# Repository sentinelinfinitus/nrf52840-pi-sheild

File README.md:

nrf52840 pi sheild

please note that this project is open for all to use and edit there own copy

time for a little background spec's for this project

the nrf52840 chip is to act as in a ncp format (more info on this below)
please note that this is the soc used in the project https://www.mouser.ca/ProductDetail/949-NRF52840-QIAA-R

more info of the soc here https://www.nordicsemi.com/Products/Low-power-short-range-wireless/nRF52840
data sheet https://www.mouser.ca/datasheet/2/297/nRF52840_OPS_v0.5-1074816.pdf
as of writing this these are to be broken out from the soc for later use

[please note]
Communication between the NCP and the host processor is via serial interface, typically using SPI or UART, over the Spinel protocol.
https://openthread.io/guides/ncp

UART, SPI, TWI, PDM, I2S, QSPI
PWM , other io
NFC-A
USB 2.0

{
[this is pulled from https://openthread.io/platforms/#network-co-processor-ncp   ]
Network Co-Processor (NCP)

The standard NCP design has Thread features on the SoC and runs the application layer on a host processor,
which is typically more capable (but has greater power demands) than the OpenThread device.
The host processor communicates with the OpenThread device via a serial interface (typically SPI or UART) over the Spinel protocol.

The benefit of this design is that the higher-power host can sleep while the 
lower-power OpenThread device remains active to maintain its place in the Thread network.
And since the SoC is not tied to the application layer,
development and testing of applications is independent of the OpenThread build.

This design is useful for gateway devices or devices that have other processing demands like IP cameras and speakers.

For more information, see NCP Support.
}

other helpfull links
https://openthread.io/guides/ncp/
https://openthread.io/guides/ncp/firmware#nordic_semiconductor_nrf52840
https://openthread.io/platforms/nrf52840

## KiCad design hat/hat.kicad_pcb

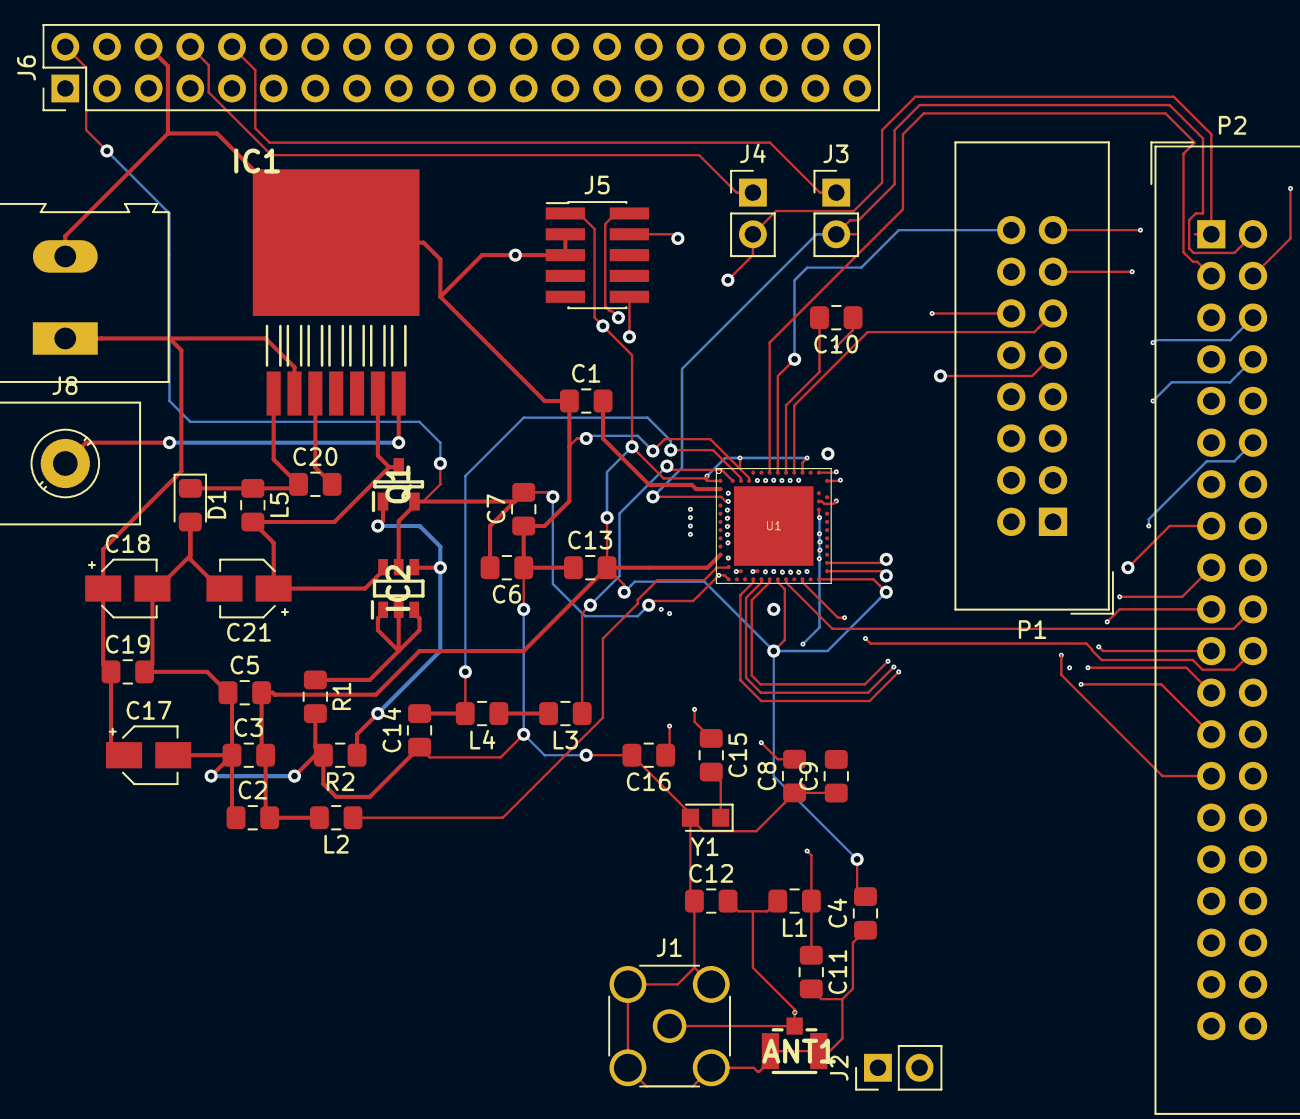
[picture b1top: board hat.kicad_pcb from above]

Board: 4 copper layers, 45 parts (0 on the bottom side), 73 nets.

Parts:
ANT1: CONUFL001-SMD
C1: 100nF; C_0805_2012Metric_Pad1.15x1.40mm_HandSolder
C2, C3, C4, C5, C13: 1.0uF; C_0805_2012Metric_Pad1.15x1.40mm_HandSolder
C6, C8: 4.7uf; C_0805_2012Metric_Pad1.15x1.40mm_HandSolder
C7: 407uF; C_0805_2012Metric_Pad1.15x1.40mm_HandSolder
C9, C10: nc; C_0805_2012Metric_Pad1.15x1.40mm_HandSolder
C11: 0.8pF; C_0805_2012Metric_Pad1.15x1.40mm_HandSolder
C12: 0.5pF; C_0805_2012Metric_Pad1.15x1.40mm_HandSolder
C14: 1.0uf; C_0805_2012Metric_Pad1.15x1.40mm_HandSolder
C15, C16: 12pf; C_0805_2012Metric_Pad1.15x1.40mm_HandSolder
C17, C18: 15uf/50v; CP_Elec_3x5.4
C19: 0.47uf; C_0805_2012Metric_Pad1.15x1.40mm_HandSolder
C20: 0.01uf; C_0805_2012Metric_Pad1.15x1.40mm_HandSolder
C21: 180uf/16v; CP_Elec_3x5.3
D1: SR305; D_0805_2012Metric_Pad1.15x1.40mm_HandSolder
IC1: LM2676S-5.0; TO127P1435X457-8N
IC2: DMMT5401-7-F; SOT95P275X110-6N
J1: Conn_Coaxial; SMA_Amphenol_132134-16_Vertical
J2: nfc; PinHeader_1x02_P2.54mm_Vertical
J3: 52840 tx pri rx; PinHeader_1x02_P2.54mm_Vertical
J4: 52840 rx rpi tx; PinHeader_1x02_P2.54mm_Vertical
J5: Conn_ARM_JTAG_SWD_10; PinHeader_2x05_P1.27mm_Vertical_SMD
J6: Raspberry_Pi_2_3; PinHeader_2x20_P2.54mm_Vertical
J7: Screw_Terminal_01x02; TerminalBlock_Altech_AK300-2_P5.00mm
J8: Screw_Terminal_01x01; TerminalBlock_MetzConnect_360271_1x01_Horizontal_ScrewM3.0_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
L1: 3.3nH; L_0805_2012Metric_Pad1.15x1.40mm_HandSolder
L2, L3, L5: 10uH; L_0805_2012Metric_Pad1.15x1.40mm_HandSolder
L4: 15nH; L_0805_2012Metric_Pad1.15x1.40mm_HandSolder
P1: Conn_02x08_Odd_Even; IDC-Header_2x08_P2.54mm_Vertical
P2: Conn_02x20_Odd_Even; IDC-Header_2x20_P2.54mm_Vertical
Q1: DMG2305UX-7; SOT96P240X100-3N
R1: 10k 1% 1005; R_0805_2012Metric_Pad1.15x1.40mm_HandSolder
R2: 47k 1% 1005; R_0805_2012Metric_Pad1.15x1.40mm_HandSolder
U1: nRF52840-QIAA
Y1: 32mhzCrystal; Crystal_SMD_2012-2Pin_2.0x1.2mm_HandSoldering

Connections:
1.1vsup_decup(dec1): C1.2, U1.C1
1.3vsup_decup(dec4): C14.2, L4.2, U1.B5
1.3vsup_decup(flash)(dec5): C9.2, U1.N24
1.3vsup_decup(rf)(dec2): C10.2, U1.A18
+12V: C17.1, C18.1, C19.1, IC1.2, J7.1
DCC: L3.1, U1.B3
DCCH: L2.1, U1.AB2
Ground (VSS_PA): ANT1.2, ANT1.3, C1.1, C2.1, C3.1, C4.1, C5.1, C6.1, C7.1, C8.1, C9.1, C10.1, C11.2, C12.1, C13.1, C14.1, C16.2, C17.2, C18.2, C19.2, C21.2, D1.2, IC1.8, J1.2, J5.3, J5.5, J6.6, J7.2, R1.2, R2.2, U1.B7, U1.F23, Y1.2
unnamed: ANT1.1, C12.2, J1.1, L1.2
unnamed: C15.2, Y1.1
unnamed: C20.1, D1.1, IC1.1, L5.1
unnamed: C20.2, IC1.3
unnamed: C21.1, IC1.6, IC2.6, L5.2, Q1.3
unnamed: IC1.7, J8.1
unnamed: IC2.1, IC2.2, IC2.3, R1.1
unnamed: IC2.4, Q1.1, R2.1
unnamed: J3.1, J6.10
unnamed: J4.1, J6.8
unnamed: L3.2, L4.1
P0.01: J3.2, P2.2, U1.F2
P0.02: P2.3, U1.A12
P0.03: P2.4, U1.B13
P0.04: P2.5, U1.J1
P0.05: P2.6, U1.K2
P0.06: P2.7, U1.L1
P0.07: P2.8, U1.M2
P0.08: P2.9, U1.N1
P0.09: J2.2, P2.10, U1.L24
P0.10: J2.1, P2.11, U1.J24
P0.11: P2.12, U1.T2
P0.12: P2.13, U1.U1
P0.13: P2.14, U1.AD8
P0.14: P2.15, U1.AC9
P0.15: P2.16, U1.AD10
P0.16: P2.17, U1.AC11
P0.17: P2.18, U1.AD12
P0.18: J5.10, U1.AC13
P0.19: P2.19, U1.AC15
P0.20: P2.20, U1.AD16
P0.21: P2.21, U1.AC17
P0.23: P2.23, U1.AC19
P0.24: P2.22, U1.AD20
P0.25: P2.25, U1.AC21
P0.26: P2.24, U1.G1
P0.27: P2.27, U1.H2
P0.28: P2.26, U1.B11
P0.29: P2.29, U1.A10
P0.30: P2.28, U1.B9
P0.31: P2.30, U1.A8
P1.00: P1.1, U1.AD22
P1.01: P1.2, U1.Y23
P1.02: P1.3, U1.W24
P1.03: P1.4, U1.V23
P1.04: P1.5, U1.U24
P1.05: P1.6, U1.T23
P1.06: P1.7, U1.R24
P1.07: P1.8, U1.P23
P1.08: P1.9, U1.P2
P1.09: P1.10, U1.R1
P1.10: P1.11, U1.A20
P1.11: P1.12, U1.B19
P1.12: P1.13, U1.B17
P1.14: P1.15, U1.B15
P1.15: P1.16, U1.A14
SWDCLK: J5.4, U1.AA24
SWDIO: J5.2, U1.AC24
VDD(A14): C2.2, C3.2, C4.2, C5.2, C13.2, J5.1, L2.2, U1.A22, U1.AD14, U1.AD23, U1.B1, U1.W1
VDDH: C6.2, C7.2, IC2.5, J6.2, Q1.2, U1.AD2, U1.Y2
XC1: C16.1, U1.B24
XC2: C15.1, U1.A23
ant: C11.1, L1.1, U1.H23
decusb3.3v: C8.2, U1.AC5
p0.00: J4.2, P2.1, U1.D2

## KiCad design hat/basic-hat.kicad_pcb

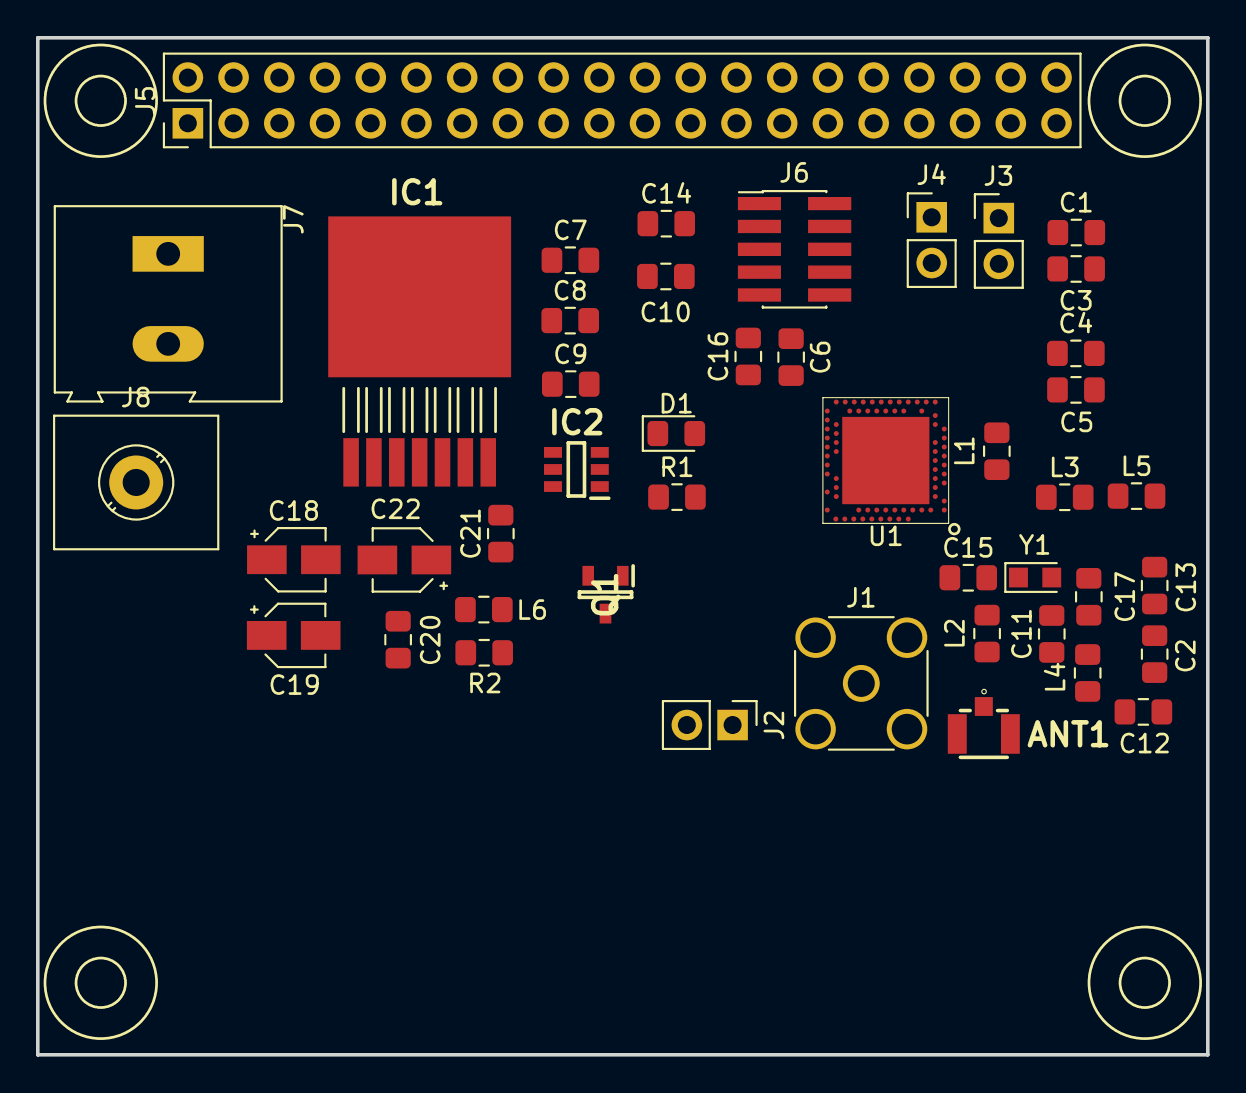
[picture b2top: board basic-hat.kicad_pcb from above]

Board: 4 copper layers, 65.0 x 56.5 mm, 45 parts (0 on the bottom side), 33 nets, no tracks yet.

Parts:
ANT1: CONUFL001-SMD
C1, C8: 4.7uF; C_0805_2012Metric_Pad1.15x1.40mm_HandSolder
C2, C5: 100nF; C_0805_2012Metric_Pad1.15x1.40mm_HandSolder
C3: 1.0uF; C_0805_2012Metric_Pad1.15x1.40mm_HandSolder
C4, C6: 100nf; C_0805_2012Metric_Pad1.15x1.40mm_HandSolder
C7, C9: 4.7uf; C_0805_2012Metric_Pad1.15x1.40mm_HandSolder
C10: 820pf; C_0805_2012Metric_Pad1.15x1.40mm_HandSolder
C11: 1.0pF; C_0805_2012Metric_Pad1.15x1.40mm_HandSolder
C12: 0.5pf; C_0805_2012Metric_Pad1.15x1.40mm_HandSolder
C13: 47nf; C_0805_2012Metric_Pad1.15x1.40mm_HandSolder
C14: 100pf; C_0805_2012Metric_Pad1.15x1.40mm_HandSolder
C15, C16: 12pf; C_0805_2012Metric_Pad1.15x1.40mm_HandSolder
C17: 1.0uf; C_0805_2012Metric_Pad1.15x1.40mm_HandSolder
C18, C19: 15uf/50v; CP_Elec_3x5.4
C20: 0.47uf; C_0805_2012Metric_Pad1.15x1.40mm_HandSolder
C21: 0.01uf; C_0805_2012Metric_Pad1.15x1.40mm_HandSolder
C22: 180uf/16v; CP_Elec_3x5.3
D1: SR305; D_0805_2012Metric_Pad1.15x1.40mm_HandSolder
IC1: LM2676S-5.0; TO127P1435X457-8N
IC2: DMMT5401-7-F; SOT95P275X110-6N
J1: Conn_Coaxial; SMA_Amphenol_132134-16_Vertical
J2: nfc; PinHeader_1x02_P2.54mm_Vertical
J3: 52840 tx pri rx; PinHeader_1x02_P2.54mm_Vertical
J4: 52840 rx rpi tx; PinHeader_1x02_P2.54mm_Vertical
J5: Raspberry_Pi_2_3; PinHeader_2x20_P2.54mm_Vertical
J6: Conn_ARM_JTAG_SWD_10; PinHeader_2x05_P1.27mm_Vertical_SMD
J7: Screw_Terminal_01x02; TerminalBlock_Altech_AK300-2_P5.00mm
J8: Screw_Terminal_01x01; TerminalBlock_MetzConnect_360271_1x01_Horizontal_ScrewM3.0_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
L1, L3, L6: 10uH; L_0805_2012Metric_Pad1.15x1.40mm_HandSolder
L2: 3.9nH; L_0805_2012Metric_Pad1.15x1.40mm_HandSolder
L4: 4.7nH; L_0805_2012Metric_Pad1.15x1.40mm_HandSolder
L5: 15nH; L_0805_2012Metric_Pad1.15x1.40mm_HandSolder
Q1: DMG2305UX-7; SOT96P240X100-3N
R1: 10k 1% 1005; R_0805_2012Metric_Pad1.15x1.40mm_HandSolder
R2: 47k 1% 1005; R_0805_2012Metric_Pad1.15x1.40mm_HandSolder
U1: nrf52840
Y1: 32mhzCrystal; Crystal_SMD_2012-2Pin_2.0x1.2mm_HandSoldering

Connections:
1.1vsup_decup(dec1): C2.2, U1.C1
1.3vsup_decup(dec4): C13.2, C17.2, L5.2, U1.B5, U1.E24
1.3vsup_decup(flash)(dec5): C10.2, U1.N24
+12V: C18.1, C19.1, C20.1, IC1.2, J7.1
DCC: L3.1, U1.B3
DCCH: L1.1, U1.AB2
Ground (VSS_PA): ANT1.2, ANT1.3, C1.1, C2.1, C3.1, C4.1, C5.1, C6.1, C7.1, C8.1, C9.1, C10.1, C11.2, C12.2, C13.1, C14.1, C16.2, C17.1, C18.2, C19.2, C20.2, C22.2, D1.2, IC1.8, J1.2, J5.6, J6.3, J6.5, J7.2, R1.2, R2.2, U1.B7, U1.F23, U1.VSS, Y1.2
unnamed: ANT1.1, C12.1, J1.1, L4.2
unnamed: C11.1, L2.2, L4.1
unnamed: C15.2, Y1.1
unnamed: C21.1, D1.1, IC1.1, L6.1
unnamed: C21.2, IC1.3
unnamed: C22.1, IC1.6, IC2.6, L6.2, Q1.3
unnamed: IC1.7, J8.1
unnamed: IC2.1, IC2.2, IC2.3, R1.1
unnamed: IC2.4, Q1.1, R2.1
unnamed: J3.1, J5.10
unnamed: J4.1, J5.8
unnamed: L3.2, L5.1
P0.01: J3.2, U1.F2
P0.09: J2.2, U1.L24
P0.10: J2.1, U1.J24
P0.18: J6.10, U1.AC13
SWDCLK: J6.4, U1.AA24
SWDIO: J6.2, U1.AC24
VDD(A22): C1.2, C3.2, C4.2, C5.2, C6.2, J6.1, L1.2, U1.A22, U1.AD14, U1.AD23, U1.B1, U1.W1
VDDH: C7.2, C8.2, IC2.5, J5.2, Q1.2, U1.AD2, U1.Y2
XC1: C16.1, U1.B24
XC2: C15.1, U1.A23
ant: L2.1, U1.H23
decusb3.3v: C9.2, U1.AC5
p0.00: J4.2, U1.D2
psu_decup(dec3): C14.2, U1.D23

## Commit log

2018-12-23 added ki cad project
    please note that i added a few parts already
    also note the files in kicad-library-master come from
    (https://github.com/ruuvi/kicad-library)
2018-12-23 updated readme + added dummy folders
    updated readme + added dummy folders
2018-12-23 added dummy files
2018-12-23 Set theme jekyll-theme-cayman
2019-01-13 made some connections
2019-02-17 minor update
    added datasheet
2019-02-19 placed labels and connectors
2019-02-19 even more connectors added
    added a ton of labels
2019-02-20 worked on schematic
    added components
2019-02-21 added ups board files
2019-03-02 updated part
    nrf52840 part updated
2019-03-02 updated file name and added sheet
    updated file name and added sheet
2019-03-03 did something don't remember
2019-03-03 started external power input schematic
    -please note this is not edited to be right it just has all the parts added based off the diagram in the lm2676 datasheet
    -power link it rpi added
2019-03-03 did some stuff tried to fix some things
    did some stuff tried to fix some things nrf52840 part keeps disappearing
2019-03-03 fixed library stuff on main pc
    please note that you will have to use the library loader to add all the right parts
2019-03-04 implemented the "ZVD" (or "ideal") diode
    implements the "ZVD" (or "ideal") diode
    reference https://github.com/raspberrypi/hats/blob/master/zvd-circuit.png
2019-03-04 did stuff
2019-03-07 did some cleanup and added power connections
    did some cleanup and added power connections
2019-03-07 worked on power
2019-03-10 did some cleanup
2019-03-11 added sma connector
2019-03-11 added sma ufl connector
2019-03-11 started pcb
2019-03-12 made more connections please note this is completely manually routed
2019-03-12 added more traces what more can i say
2019-03-12 more traces added
2019-03-25 added reference files
2019-03-25 minor organisation
2019-03-26 started custom part
2019-03-27 added footprint and guideline for footprint
    added footprint and guideline for footprint
2019-03-27 nrf52840 footprint nearing completion
    nrf52840 footprint nearing completion
2019-03-28 nrf52840 part v0.1
    nrf52840 part v0.1
2019-03-28 added basic varient
2019-03-31 vega
2019-04-01 basicly done basic version
    NOT COMPLEATED YET but close
2019-04-02 exported gerber files
2019-04-02 minor errors fixed
2019-05-06 optimized layout
